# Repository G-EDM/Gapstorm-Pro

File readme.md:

</br>
</br>
</br>

```diff
 ______     _______ ______  _______
|  ____ ___ |______ |     \ |  |  |
|_____|     |______ |_____/ |  |  |
```                                                               

</br>
</br>

# G-EDM Gapstorm Pro
</br>

</br>
</br>

The files provided on this repo are fully OpenSource. Have fun. No warranties!

# (fresh update) First test for max current

I just made an initial test for max current without risking the big FET. Connected two parallel IRFP260N to the screw terminals of the board and was able to push 9.5A without breaking anything.

The big FET has a much lower RDSon resistance so there is still a chance that it may not take the full 9.5A but this looks very good so far. No warranty on that but I think the big FET will also be able to manage the full DPH8909 current.

# Warning

This repo contains the upgrade Gapstorm PCB files. I already assembled the board but did not yet had time for real tests. I made a short test shorting the wires at 2.5A and everything looked good. Feedback was very nice. Once I'm done testing, a link to PCBway will be provided and the max current rating published too. For people that have the initial Gapstorm PCB I recommend to change the Gate resistor against a 100R resistor as it is on this board. The Mosfet switching happens so rapid that very high inrush currents can occur that can damage the FET. Even with the 100R resistor the Mosfet is very very fast switching without visible slope on the ESP scope.

</br>
</br>

# About
</br>
The Gapstorm Pro is an improved version for the switching PCB used to control the discharges for EDM machines.
</br>
The PCB is not a stand alone arc generator and requires a DPM8605 or DPH8909 as external power source.
</br>
</br>

# Features
* Mosfet low side switch
* Foil pulse capacitor
* Optically isolated voltage and current feedback
* Optically isolated PWM input
</br>
</br>

# Current and Voltage ratings

* Max input voltage on the power inputs is designed to be 80V. The board has TVS and Zener protection diodes and the input should not exceed 80v. 70V is my personal sweetspot.

* In regards of max current there is still some research that needs to be done. Depending on the Gate resistor and the Foil cap there can occur very high inrush currents that can easily destroy the Mosfet. I changed the Gate resistor to a higher value to prevent this from easily happening but have not produced real max rating data as of now. The Mosfet is expenssive and I am too broke to burn through things.  I'm working on that. 
</br>
</br>

# Wiring

* The board requires a 5P JST XH wire to connect with the motionboard

* A little 12v PSU is required for the gate drive. I use a Mean Well APV-35-12 LED 12V 2.4A for that.

* DPM/DPH positive output connects to Power+ and negative to Power-. Note that those terminals are not next to eachother on this board.

* The two center terminals are the spark terminals. Spark+ connects to the work and Spark- to the electrode.

</br>
</br>

# Important Notes and Warnings

* The Mosfet requires good cooling. It can be screwed onto a heatsick or inside a metal enclosure with the PCB just sitting on top of it.
No isolation barrier between the Mosfet and the colling component is required as the SOT227 Package already provides isolation.

* The switching section is a low side switch and thereforewhile the Mosfet is active DRAIN is switched to GND
The voltage feedback is measured from Work to Electrode using a voltage divider to scale the voltage down and feed it into a sensing circuit.
The nature of this makes a measurement in the OnTime of the switching impossible since the voltage drops close to GND and the input for the sensing circuit looks like a squarewave. This allows proximity sensing but not real gap voltage sensing and then OnTime requires to be filtered out via software.

</br>
</br>

# DPM8605 or DPH8909

* One of those devices is required as source for the spark. I recommend the DPH8909 as it allows higher voltages but the DPM8605 is ok too but limited to 60V.

* Those step down converters come with different interfaces. In order to connect them to the motionboard and have the firmware communicate with them the TTL version is required. Not the RF (Radio) or RS485! Also the baudrate needs to be set at the highest available to match the baudrate used in the firmware. See the manual for the device and search for BAUD. 115200 is what it needs to be and this number is shown on the little display as 115.2 or something.

* Set the current to 1.6A or 1.8A before the first run. This is normally the current I use and safe. Voltage either 70v or if the DPM8605 is used 60v.

</br>
</br>

# G-EDM Wiki

[A little Wiki can be found here](https://gedm.org/wiki)

</br>
</br>

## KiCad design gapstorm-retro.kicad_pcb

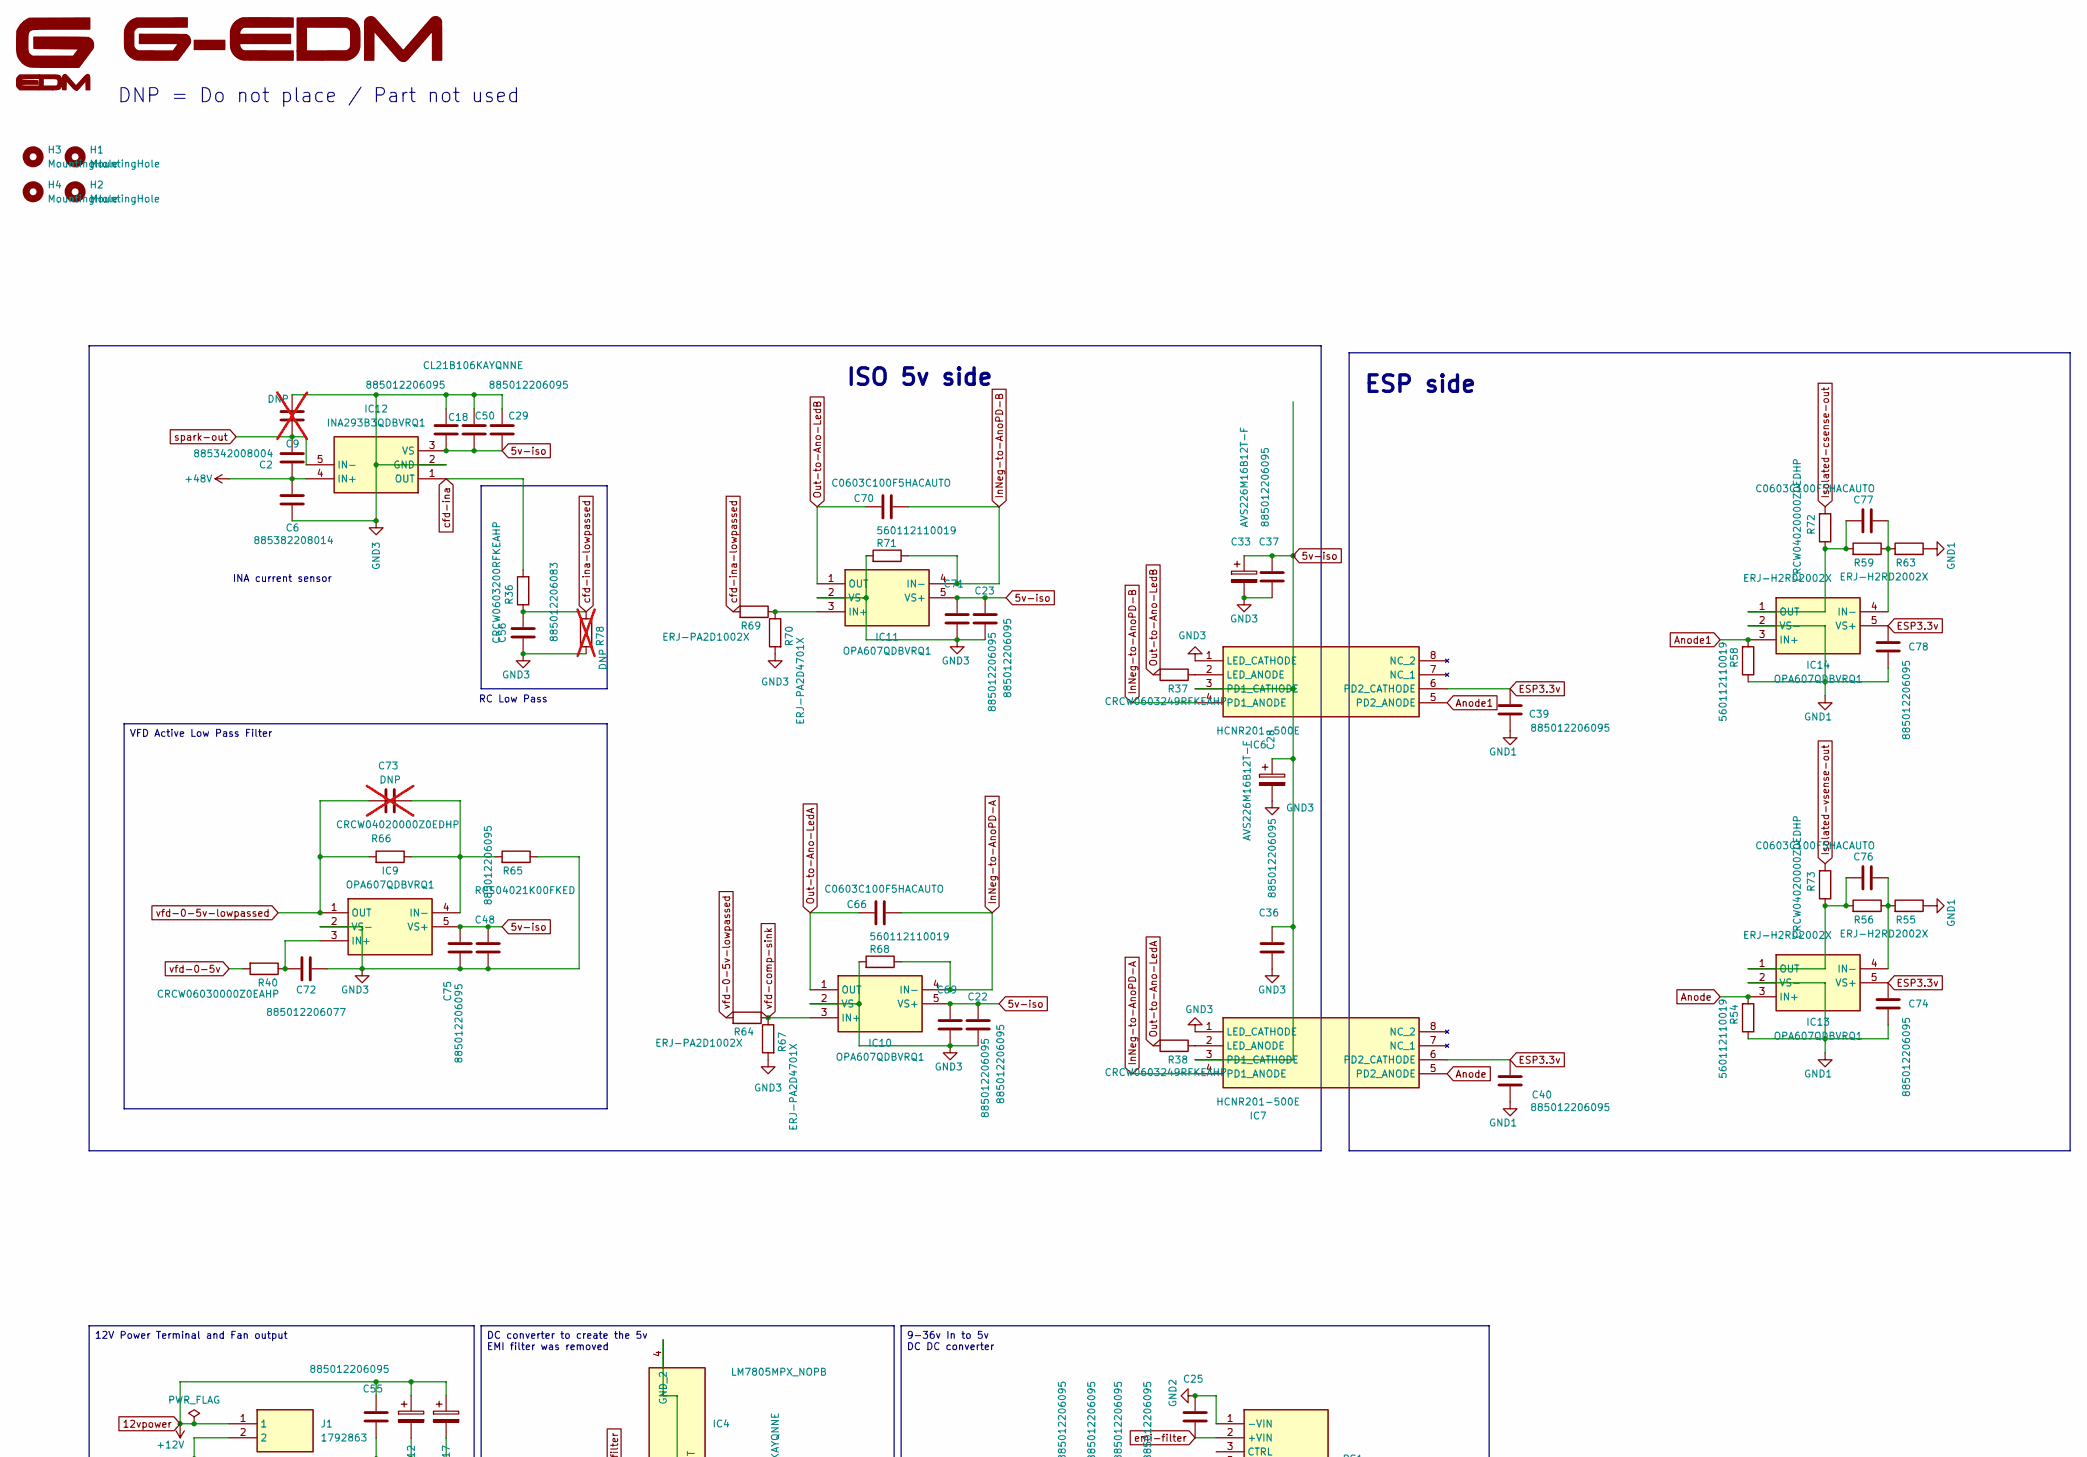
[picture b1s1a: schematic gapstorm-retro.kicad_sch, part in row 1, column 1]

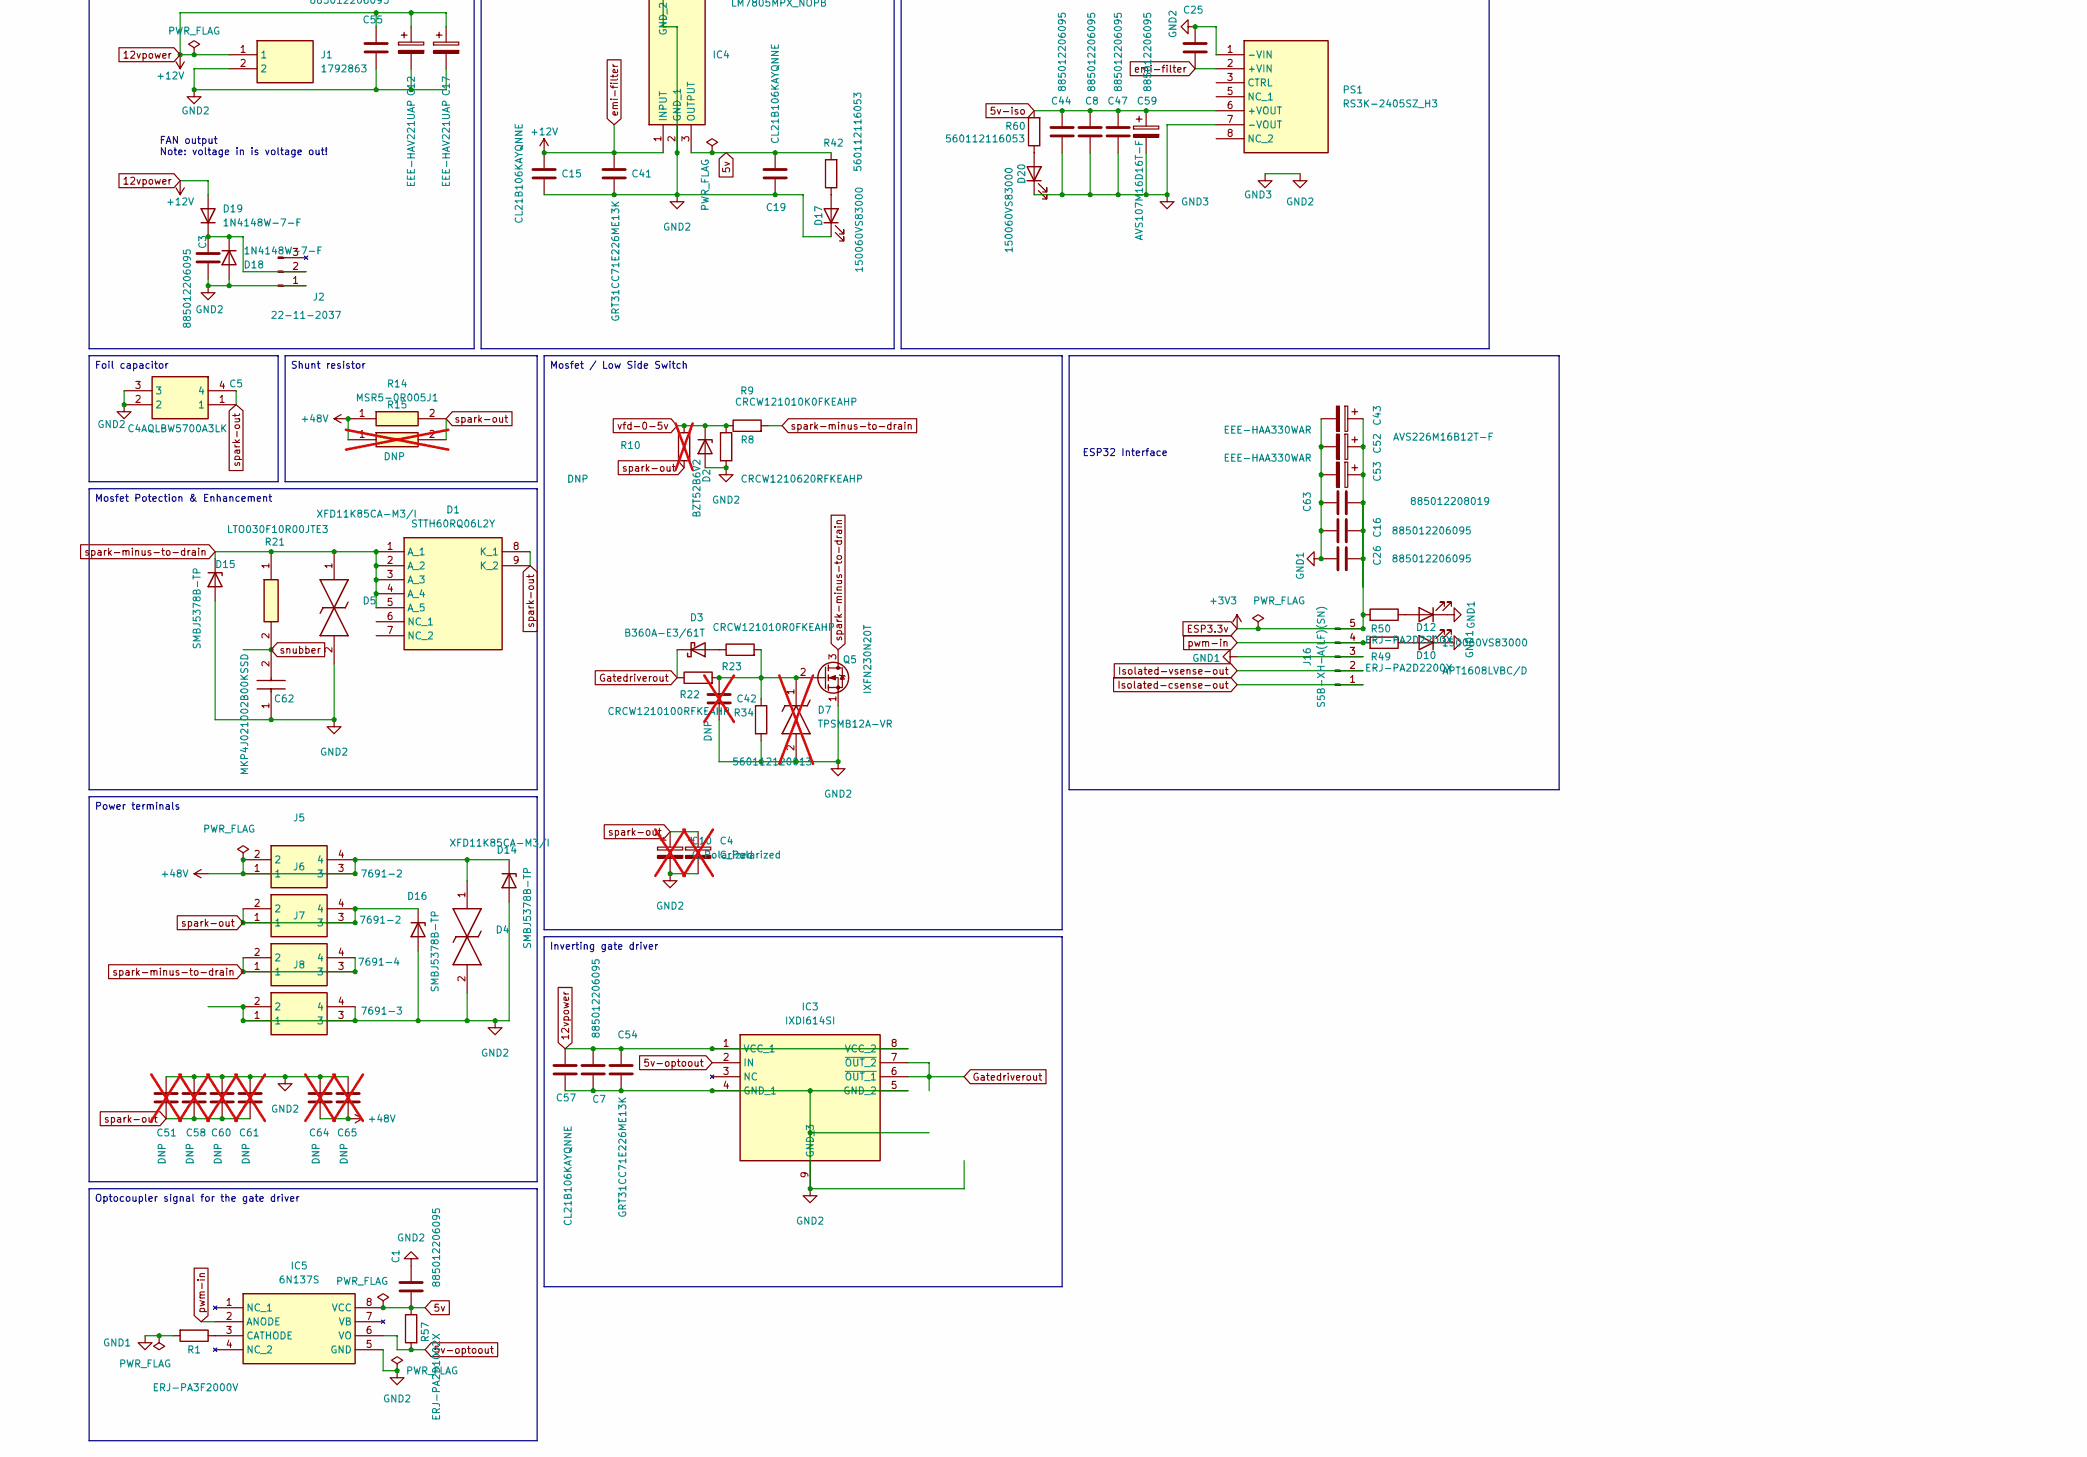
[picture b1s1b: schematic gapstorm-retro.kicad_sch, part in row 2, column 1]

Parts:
C1, C3, C7, C8, C16, C18, C22, C23, C25, C26, C29, C36, C37, C39, C40, C44, C47, C48, C55, C69, C71, C74, C75, C78: 885012206095; C_0603_1608Metric_Pad1.08x0.95mm_HandSolder
C2: 885342008004; C_1206_3216Metric_Pad1.33x1.80mm_HandSolder
C4, C10: C_Polarized; C_Radial_D12.5mm_H25.0mm_P5.00mm; not fitted
C5: C4AQLBW5700A3LK; Manufacturer_Part_Number C4AQLBW5700A3LK; Mouser Part Number 80-C4AQLBW5700A3LK
C6: 885382208014; C_1206_3216Metric_Pad1.33x1.80mm_HandSolder
C9, C42, C51, C58, C60, C61, C64, C65: DNP; C_1206_3216Metric_Pad1.33x1.80mm_HandSolder; not fitted
C12, C17: EEE-HAV221UAP; CP_Elec_8x10.5
C15, C19, C50, C57: CL21B106KAYQNNE; C_0805_2012Metric_Pad1.18x1.45mm_HandSolder
C28, C33, C43: AVS226M16B12T-F; CP_Elec_4x5.4
C41, C54: GRT31CC71E226ME13K; C_1206_3216Metric_Pad1.33x1.80mm_HandSolder
C52, C53: EEE-HAA330WAR; CP_Elec_4x5.4
C56: 885012206083; C_0603_1608Metric_Pad1.08x0.95mm_HandSolder
C59: AVS107M16D16T-F; CP_Elec_6.3x5.4
C62: MKP4J021002B00KSSD; C_Rect_L10.0mm_W4.0mm_P7.50mm_MKS4; Manufacturer_Part_Number FKP2G011001D00KI00; Mouser Part Number 505-FKP2G011001D00KI
C63: 885012208019; C_1206_3216Metric_Pad1.33x1.80mm_HandSolder
C66, C70, C76, C77: C0603C100F5HACAUTO; C_0603_1608Metric_Pad1.08x0.95mm_HandSolder
C72: 885012206077; C_0603_1608Metric_Pad1.08x0.95mm_HandSolder
C73: DNP; C_0603_1608Metric_Pad1.08x0.95mm_HandSolder; not fitted
D1: STTH60RQ06L2Y; Manufacturer_Part_Number STTH60RQ06L2Y
D2: BZT52B6V2; D_SOD-123F
D3: B360A-E3/61T; D_SMA_Handsoldering
D4, D5: XFD11K85CA-M3/I; SM8A27HE32D; Manufacturer_Part_Number PTVS1-086C-H; Mouser Part Number 652-PTVS1-086C-H
D7: TPSMB12A-VR; DIOM5436X244N; Manufacturer_Part_Number TPSMB12A-VR; Mouser Part Number 576-TPSMB12A-VR; not fitted
D10: APT1608LVBC/D; LED_0603_1608Metric_Pad1.05x0.95mm_HandSolder
D12, D17, D20: 150060VS83000; LED_0603_1608Metric_Pad1.05x0.95mm_HandSolder
D14, D15, D16: SMBJ5378B-TP; D_SMB_Handsoldering
D18, D19: 1N4148W-7-F; D_SOD-123
H1, H2, H3, H4: MountingHole; MountingHole_3.2mm_M3_Pad_Via
IC3: IXDI614SI; SOIC127P600X170-9N; Manufacturer_Part_Number IXDI614SI; Mouser Part Number 849-IXDI614SI
IC4: LM7805MPX_NOPB; SOT230P700X180-4N; Manufacturer_Part_Number LM7805MPX/NOPB; Mouser Part Number 595-LM7805MPX/NOPB
IC5: 6N137S; SOP254P1016X460-8N; Manufacturer_Part_Number 6N136S; Mouser Part Number 859-6N136S
IC6, IC7: HCNR201-500E; SOP254P1230X400-8N; Manufacturer_Part_Number HCNR201-500E; Mouser Part Number 630-HCNR201-500E
IC9, IC10, IC11, IC13, IC14: OPA607QDBVRQ1; SOT95P280X145-5N; Manufacturer_Part_Number OPA607QDBVRQ1; Mouser Part Number 595-OPA607QDBVRQ1
IC12: INA293B3QDBVRQ1; SOT95P280X145-5N; Manufacturer_Part_Number INA293B1QDBVRQ1; Mouser Part Number 595-INA293B1QDBVRQ1
J1: 1792863; Manufacturer_Part_Number 1792863; Mouser Part Number 651-1792863
J2: 22-11-2037; FanPinHeader_1x03_P2.54mm_Vertical
J5, J6: 7691-2; 8191SEMS; Manufacturer_Part_Number 8191-SEMS; Mouser Part Number 534-8191-SEMS
J7: 7691-4; 8191SEMS; Manufacturer_Part_Number 8191-SEMS; Mouser Part Number 534-8191-SEMS
J8: 7691-3; 8191SEMS; Manufacturer_Part_Number 8191-SEMS; Mouser Part Number 534-8191-SEMS
J16: S5B-XH-A(LF)(SN); JST_XH_S5B-XH-A_1x05_P2.50mm_Horizontal
PS1: RS3K-2405SZ_H3; RS3K2405SZH3; Manufacturer_Part_Number RS3K-2405SZ/H3; Mouser Part Number 919-RS3K-2405SZ/H3
Q5: IXFN230N20T; SOT-227
R1: ERJ-PA3F2000V; R_0603_1608Metric_Pad0.98x0.95mm_HandSolder
R8: CRCW1210620RFKEAHP; R_1210_3225Metric_Pad1.30x2.65mm_HandSolder
R9: CRCW121010K0FKEAHP; R_1210_3225Metric_Pad1.30x2.65mm_HandSolder
R10: DNP; R_1210_3225Metric_Pad1.30x2.65mm_HandSolder; not fitted
R14: MSR5-0R005J1; MSR50R1F1; Manufacturer_Part_Number MSR5-0R1F1
R15: DNP; MSR50R1F1; Manufacturer_Part_Number MSR5-0R1F1; not fitted
R21: LTO030F10R00JTE3; TO508P350X1040X2030-2P; Manufacturer_Part_Number LTO030F10R00JTE3; Mouser Part Number 72-LTO030F10R00JTE3
R22: CRCW1210100RFKEAHP; R_1210_3225Metric_Pad1.30x2.65mm_HandSolder
R23: CRCW121010R0FKEAHP; R_1210_3225Metric_Pad1.30x2.65mm_HandSolder
R34: 560112120013; R_0805_2012Metric_Pad1.20x1.40mm_HandSolder
R36: CRCW0603200RFKEAHP; R_0603_1608Metric_Pad0.98x0.95mm_HandSolder
R37, R38: CRCW0603249RFKEAHP; R_0603_1608Metric_Pad0.98x0.95mm_HandSolder
R40: CRCW06030000Z0EAHP; R_0603_1608Metric_Pad0.98x0.95mm_HandSolder
R42, R60: 560112116053; R_0603_1608Metric_Pad0.98x0.95mm_HandSolder
R49, R50: ERJ-PA2D2200X; R_0402_1005Metric_Pad0.72x0.64mm_HandSolder
R54, R58, R68, R71: 560112110019; R_0402_1005Metric_Pad0.72x0.64mm_HandSolder
R55, R56, R59, R63: ERJ-H2RD2002X; R_0402_1005Metric_Pad0.72x0.64mm_HandSolder
R57, R64, R69: ERJ-PA2D1002X; R_0402_1005Metric_Pad0.72x0.64mm_HandSolder
R65: RCS04021K00FKED; R_0402_1005Metric_Pad0.72x0.64mm_HandSolder
R66, R72, R73: CRCW04020000Z0EDHP; R_0402_1005Metric_Pad0.72x0.64mm_HandSolder
R67, R70: ERJ-PA2D4701X; R_0402_1005Metric_Pad0.72x0.64mm_HandSolder
R78: DNP; R_0402_1005Metric_Pad0.72x0.64mm_HandSolder; not fitted

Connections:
5v: C1.1, C19.2, IC4.3 (OUTPUT), IC5.8 (VCC), R42.2, R57.1
5v-iso: C8.2, C18.2, C22.1, C23.1, C28.1, C29.1, C33.1, C36.2, C37.2, C44.1, C47.1, C48.1, C50.1, C59.1, C69.2, C71.2, C75.1, IC6.3 (PD1_CATHODE), IC7.3 (PD1_CATHODE), IC9.5 (VS+), IC10.5 (VS+), IC11.5 (VS+), IC12.3 (VS), PS1.6 (+VOUT), R60.2
5v-optoout: IC3.2 (IN), IC5.6 (VO), R57.2
12vpower: C7.2, C12.1, C15.2, C17.1, C25.1, C41.1, C54.1, C55.1, C57.2, D19.2 (A), IC3.1 (VCC_1), IC3.8 (VCC_2), IC4.1 (INPUT), J1.1, PS1.2 (+VIN)
+48V: C2.2, C6.1, C64.1, C65.1, D4.1, D14.1 (K), IC12.4 (IN+), J5.1, J5.2, J5.3, J5.4, R14.1, R15.1
Anode: IC7.5 (PD2_ANODE), IC13.3 (IN+), R54.2
Anode1: IC6.5 (PD2_ANODE), IC14.3 (IN+), R58.2
ESP3.3v: C16.1, C26.1, C39.1, C40.1, C43.1, C52.1, C53.1, C63.2, C74.1, C78.1, IC6.6 (PD2_CATHODE), IC7.6 (PD2_CATHODE), IC13.5 (VS+), IC14.5 (VS+), J16.5, R50.2
GND1: C16.2, C26.2, C39.2, C40.2, C43.2, C52.2, C53.2, C63.1, C74.2, C78.2, D10.1 (K), D12.1 (K), IC13.2 (VS-), IC14.2 (VS-), J16.3, R1.2, R54.1, R55.1, R58.1, R63.1
GND2: C1.2, C3.1, C4.2, C5.2, C5.3, C6.2, C7.1, C8.1, C9.1, C10.2, C12.2, C15.1, C17.2, C18.1, C19.1, C22.2, C23.2, C25.2, C28.2, C29.2, C33.2, C36.1, C37.1, C41.2, C42.2, C44.2, C47.2, C48.2, C50.2, C51.2, C54.2, C55.2, C56.1, C57.1, C58.2, C59.2, C60.2, C61.2, C62.1, C64.2, C65.2, C69.1, C71.1, C72.1, C75.2, D2.2 (A), D4.2, D5.2, D7.2 (A), D14.2 (A), D15.2 (A), D16.2 (A), D17.1 (K), D18.2 (A), D20.1 (K), IC3.4 (GND_1), IC3.5 (GND_2), IC3.9 (GND_3), IC4.2 (GND_1), IC4.4 (GND_2), IC5.5 (GND), IC6.1 (LED_CATHODE), IC7.1 (LED_CATHODE), IC9.2 (VS-), IC10.2 (VS-), IC11.2 (VS-), IC12.2 (GND), J1.2, J2.1, J8.1, J8.2, J8.3, J8.4, PS1.1 (-VIN), PS1.7 (-VOUT), Q5.1 (S), Q5.4 (S), R8.2, R34.2, R65.1, R67.2, R68.2, R70.2, R71.2, R78.2
Gatedriverout: D3.1 (K), IC3.6 (~OUT_1), IC3.7 (~OUT_2), R22.1
InNeg-to-AnoPD-A: C66.2, IC7.4 (PD1_ANODE), IC10.4 (IN-), R68.1
InNeg-to-AnoPD-B: C70.2, IC6.4 (PD1_ANODE), IC11.4 (IN-), R71.1
Isolated-csense-out: J16.1, R72.2
Isolated-vsense-out: J16.2, R73.2
unnamed: D3.2 (A), R23.1
unnamed: C42.1, D7.1 (K), Q5.2 (G), R22.2, R23.2, R34.1
unnamed: D10.2 (A), R49.1
unnamed: D12.2 (A), R50.1
unnamed: D17.2 (A), R42.1
unnamed: C3.2, D18.1 (K), D19.1 (K), J2.2
unnamed: D20.2 (A), R60.1
unnamed: IC5.3 (CATHODE), R1.1
unnamed: IC6.2 (LED_ANODE), R37.1
unnamed: IC7.2 (LED_ANODE), R38.1
unnamed: C72.2, IC9.3 (IN+), R40.1
unnamed: C73.1, IC9.4 (IN-), R65.2, R66.1
unnamed: IC11.3 (IN+), R69.1, R70.1
unnamed: C76.2, IC13.4 (IN-), R55.2, R56.1
unnamed: C76.1, IC13.1 (OUT), R56.2, R73.1
unnamed: C77.2, IC14.4 (IN-), R59.1, R63.2
unnamed: C77.1, IC14.1 (OUT), R59.2, R72.1
Out-to-Ano-LedA: C66.1, IC10.1 (OUT), R38.2
Out-to-Ano-LedB: C70.1, IC11.1 (OUT), R37.2
cfd-ina: IC12.1 (OUT), R36.2
cfd-ina-lowpassed: C56.2, R36.1, R69.2, R78.1
pwm-in: IC5.2 (ANODE), J16.4, R49.2
snubber: C62.2, R21.2
spark-minus-to-drain: D1.1 (A_1), D1.2 (A_2), D1.3 (A_3), D1.4 (A_4), D1.5 (A_5), D5.1, D15.1 (K), J7.1, J7.2, J7.3, J7.4, Q5.3 (D), R9.2, R21.1
spark-out: C2.1, C4.1, C5.1, C5.4, C9.2, C10.1, C51.1, C58.1, C60.1, C61.1, D1.8 (K_1), D1.9 (K_2), D16.1 (K), IC12.5 (IN-), J6.1, J6.2, J6.3, J6.4, R10.2, R14.2, R15.2
vfd-0-5v: D2.1 (K), R8.1, R9.1, R10.1, R40.2
vfd-0-5v-lowpassed: C73.2, IC9.1 (OUT), R64.2, R66.2
vfd-comp-sink: IC10.3 (IN+), R64.1, R67.1

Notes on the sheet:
FAN output Note: voltage in is voltage out!
DNP = Do not place / Part not used
RC Low Pass
ESP32 Interface
INA current sensor
ESP side
ISO 5v side
VFD Active Low Pass Filter
Shunt resistor
Power terminals
Inverting gate driver
12V Power Terminal and Fan output
Foil capacitor
Optocoupler signal for the gate driver
Mosfet / Low Side Switch
Mosfet Potection & Enhancement
9-36v In to 5v DC DC converter
DC converter to create the 5v EMI filter was removed

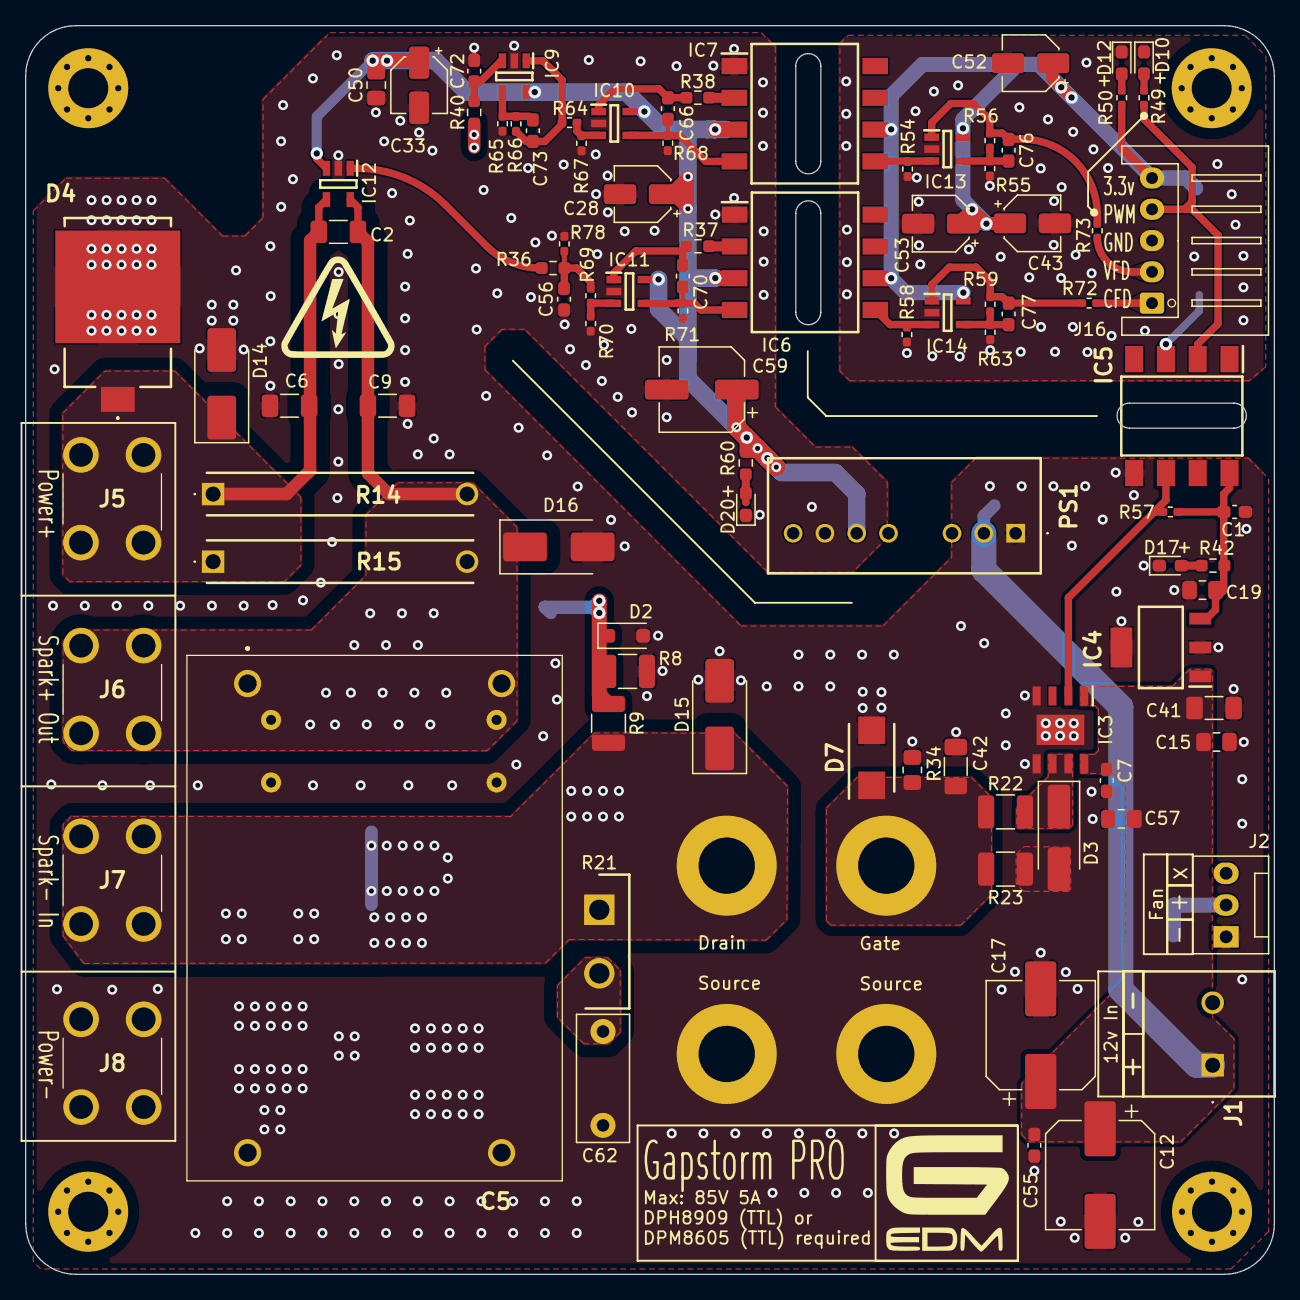
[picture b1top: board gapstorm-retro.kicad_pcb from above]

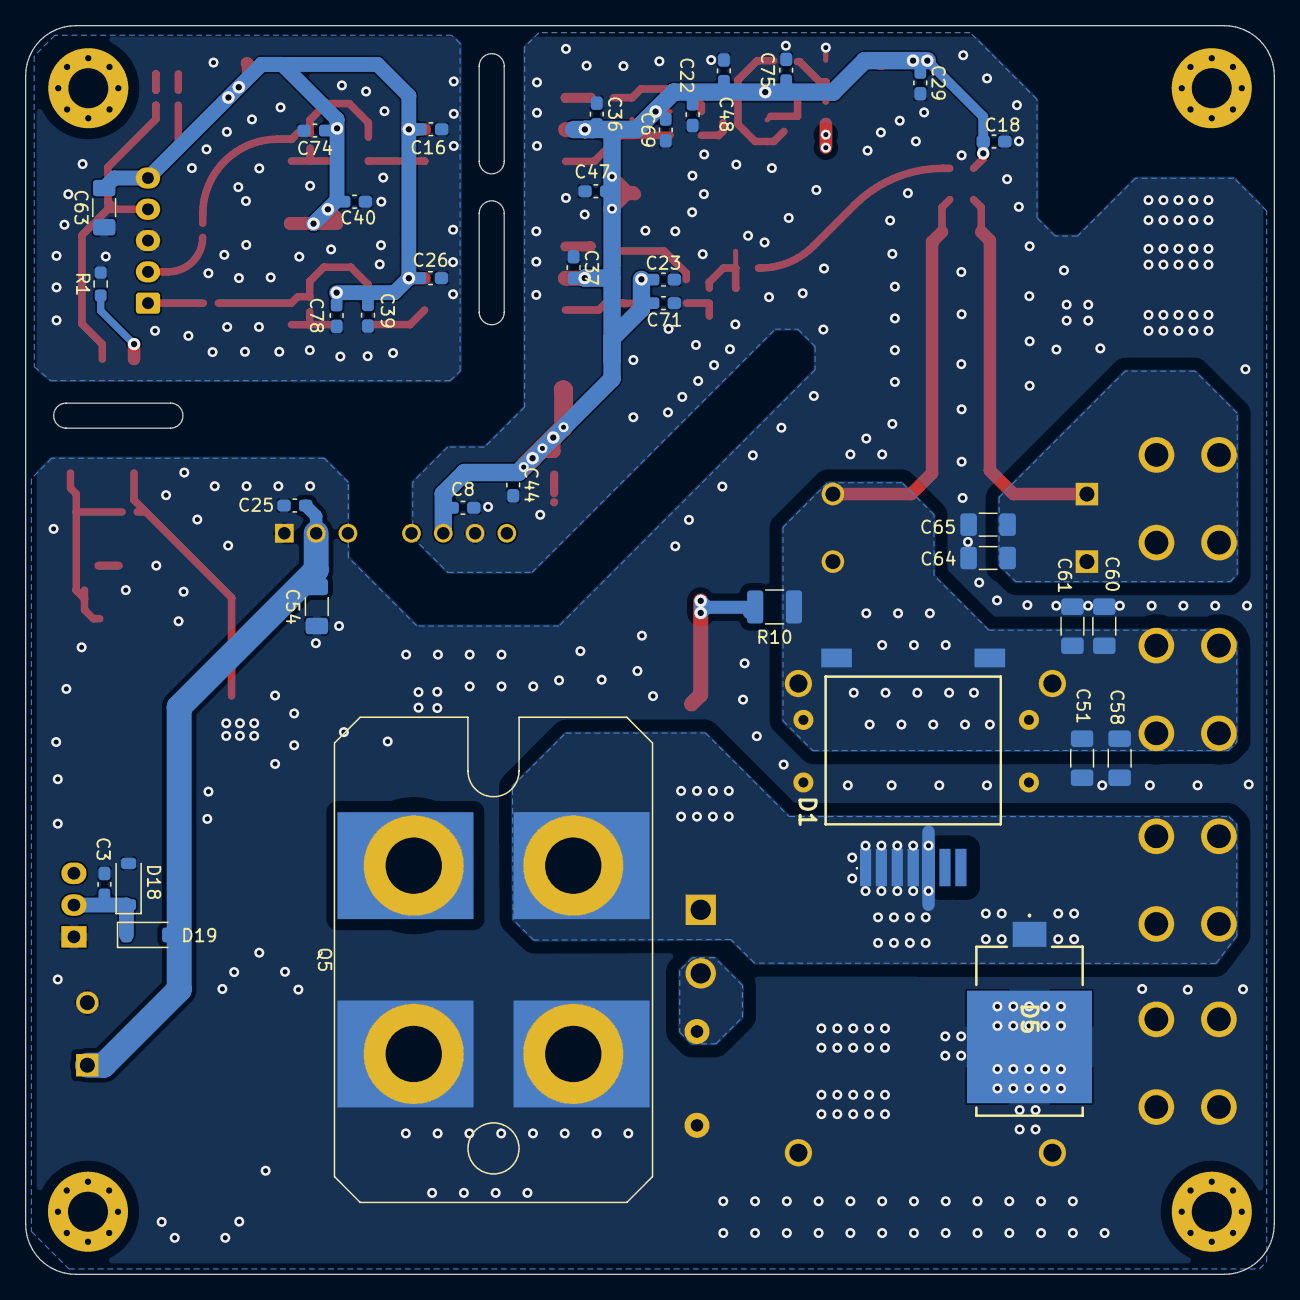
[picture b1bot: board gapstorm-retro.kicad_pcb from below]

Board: 4 copper layers, 99.8 x 99.8 mm, 135 parts (36 on the bottom side), 43 nets.

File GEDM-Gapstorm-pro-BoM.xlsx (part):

|  |  | G-EDM Pulseboard Gapstorm Pro
Item # | *Designator | *Qty | Manufacturer | *Mfg Part # | Description / Value | *Package/Footprint | Type | Comments
1 | C1, C3, C7, C8, C16, C18, C22, C23, C26, C36, C37, C39, C40, C47, C48, C55, C69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 | 24 | Würth Elektronik | 885012206095 | Multilayer Ceramic Capacitors MLCC - SMD/SMT WCAP-CSGP 0.1uF 0603 10% 50V MLCC | C_0603_1608Metric_Pad1.08x0.95mm_HandSolder | SMD
2 | C2 | 1 | Würth Elektronik | 885342008004 | Multilayer Ceramic Capacitors MLCC - SMD/SMT WCAP-CSMH 630V 100pF 1206 5% | C_1206_3216Metric_Pad1.33x1.80mm_HandSolder | SMD
3 | C4, C10 | 0 |  |  | Do not place / Part not used | C_Radial_D12.5mm_H25.0mm_P5.00mm | THT | Do not place / Part not used
4 | C5 | 1 | KEMET | C4AQLBW5700A3LK | Film Capacitors 500V 70 uF 105C 10% 4 Pin LS=37.5 mm AEC-Q200 | C4AQLBW5700A3LK | THT
5 | C6 | 1 | Würth Elektronik | 885382208014 | Multilayer Ceramic Capacitors MLCC - SMD/SMT WCAP-CSST 1206 680pF 10% 2000VDC | C_1206_3216Metric_Pad1.33x1.80mm_HandSolder | SMD
6 | C9, C42, C51, C58, C60, C61, C64, C65 | 0 |  |  | Do not place / Part not used | C_1206_3216Metric_Pad1.33x1.80mm_HandSolder | SMD | Do not place / Part not used
7 | C12, C17 | 2 | Panasonic Industry | EEE-HAV221UAP | Aluminium Electrolytic Capacitors - SMD 220UF 35V HA SMD | CP_Elec_8x10.5 | SMD
8 | C15, C19, C50, C57 | 4 | Samsung Electro-Mechanics | CL21B106KAYQNNE | Multilayer Ceramic Capacitors MLCC - SMD/SMT 10uF 25V X7R 10% 080 0805 | C_0805_2012Metric_Pad1.18x1.45mm_HandSolder | SMD
9 | C28, C33, C43 | 3 | Knowles / Illinois Capacitor | AVS226M16B12T-F | Aluminium Electrolytic Capacitors - SMD 16V 22uF AEC-Q200 | CP_Elec_4x5.4 | SMD
10 | C41, C54 | 2 | Murata Electronics | GRT31CC71E226ME13K | Multilayer Ceramic Capacitors MLCC - SMD/SMT 1206 22uF 25VDC 20% X7S AEC-Q200 | C_1206_3216Metric_Pad1.33x1.80mm_HandSolder | SMD
11 | C52, C53 | 2 | Panasonic Industry | EEE-HAA330WAR | Aluminium Electrolytic Capacitors - SMD 33UF 10V HA SMD | CP_Elec_4x5.4 | SMD
12 | C56 | 1 | Würth Elektronik | 885012206083 | Multilayer Ceramic Capacitors MLCC - SMD/SMT WCAP-CSGP 1000pF 0603 10% 50V MLCC | C_0603_1608Metric_Pad1.08x0.95mm_HandSolder | SMD
13 | C59 | 1 | Knowles / Illinois Capacitor | AVS107M16D16T-F | Aluminium Electrolytic Capacitors - SMD 16V 100uF AEC-Q200 | CP_Elec_6.3x5.4 | SMD
14 | C62 | 1 | WIMA | MKP4J021002B00KSSD | Film Capacitors 630V .01uF 10% | C_Rect_L10.0mm_W4.0mm_P7.50mm_MKS4 | THT
15 | C63 | 1 | Würth Elektronik | 885012208019 | Multilayer Ceramic Capacitors MLCC - SMD/SMT WCAP-CSGP 22uF 1206 10% 10V MLCC | C_1206_3216Metric_Pad1.33x1.80mm_HandSolder | SMD
16 | C66, C70, C76, C77 | 4 | KEMET | C0603C100F5HACAUTO | Multilayer Ceramic Capacitors MLCC - SMD/SMT 50V 10pF 0603 X8R 1% AEC-Q200 | C_0603_1608Metric_Pad1.08x0.95mm_HandSolder | SMD
17 | C72 | 1 | Würth Elektronik | 885012206077 | Multilayer Ceramic Capacitors MLCC - SMD/SMT WCAP-CSGP 100pF 0603 10% 50V MLCC | C_0603_1608Metric_Pad1.08x0.95mm_HandSolder | SMD
18 | C73 | 0 |  |  | Do not place / Part not used | C_0603_1608Metric_Pad1.08x0.95mm_HandSolder | SMD | Do not place / Part not used
19 | D1 | 1 | STMicroelectronics | STTH60RQ06L2Y | Rectifiers Automotive 600 V, 60 A ultrafast high voltage rectifier | STTH60RQ06L2Y | SMD
20 | D2 | 0 |  |  | Do not place / Part not used | D_SOD-123F | SMD | Do not place / Part not used
21 | D3 | 1 | Vishay Semiconductors | B360A-E3/61T | Schottky Diodes & Rectifiers 60 Volt 3.0 Amp 50 Amp IFSM | D_SMA_Handsoldering | SMD
22 | D4, D5 | 2 | Vishay Semiconductors | XFD11K85CA-M3/I | ESD Protection Diodes / TVS Diodes 11KW, 85V 5%, SMD FlatClamping TVS | SM8A27HE32D | SMD
23 | D7 | 0 |  |  | Do not place / Part not used | DIOM5436X244N | SMD | Do not place / Part not used
24 | D10 | 1 | Kingbright | APT1608LVBC/D | Single Colour LEDs 1.6X0.8MM LOW CRNT | LED_0603_1608Metric_Pad1.05x0.95mm_HandSolder | SMD
25 | D12, D17, D20 | 3 | Würth Elektronik | 150060VS83000 | Single Colour LEDs WL-SMCW SMT 0603 Dome Bright Green Typ 300mcd 2V | LED_0603_1608Metric_Pad1.05x0.95mm_HandSolder | SMD
26 | D14, D15, D16 | 3 | Micro Commercial Components (MCC) | SMBJ5378B-TP | Zener Diodes 5W ZENERS SMB 100V | D_SMB_Handsoldering | SMD
27 | D18, D19 | 2 | Diodes Incorporated | 1N4148W-7-F | Small Signal Switching Diodes SURFACE MOUNT FAST SWITCHING DIODE 2A | D_SOD-123 | SMD
28 | IC3 | 1 | IXYS Integrated Circuits | IXDI614SI | Gate Drivers 14-Ampere Low-Side Ultrafast MOSFET Inverting | SOIC127P600X170-9N | SMD
29 | IC4 | 1 | Texas Instruments | LM7805MPX_NOPB | Linear Voltage Regulators 1.5-A 30-V linear vo ltage regulator 4- A 595-LM7805M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 | SOT230P700X180-4N | SMD
30 | IC5 | 1 | LITEON | 6N137S | High Speed Optocouplers High Speed 10MBd LogicGate Output | SOP254P1016X460-8N | SMD
31 | IC6, IC7 | 2 | Broadcom / Avago | HCNR201-500E | High Linearity Optocouplers 1 Ch 60mW 25mA | SOP254P1230X400-8N | SMD
32 | IC9, IC10, IC11, IC13, IC14 | 5 | Texas Instruments | OPA607QDBVRQ1 | High Speed Operational Amplifiers Automotive 50-MHz lo w-power gain of 6 | SOT95P280X145-5N | SMD
33 | IC12 | 1 | Texas Instruments | INA293B3QDBVRQ1 | Current Sense Amplifiers AEC-Q100 -4-V to 11 0-V 1.3-MHz ultra-fast | SOT95P280X145-5N | SMD
34 | J1 | 1 | Phoenix Contact | 1792863 | Fixed Terminal Blocks PTS 1,5/ 2-5,0-H | 1792863 | THT
35 | J2 | 1 | Molex | 22-11-2037 | Headers & Wire Housings KK 100 Hdr FrLk Vert 3CKT - 2P Voided | FanPinHeader_1x03_P2.54mm_Vertical | THT
36 | J5, J6 | 2 | Keystone Electronics | 7691-2 | Terminals SCREW TERMINAL RED | 8191SEMS | THT
37 | J7 | 1 | Keystone Electronics | 7691-4 | Terminals SCREW TERMINAL WHITE | 8191SEMS | THT
38 | J8 | 1 | Keystone Electronics | 7691-3 | Terminals SCREW TERMINAL BLACK | 8191SEMS | THT
39 | J16 | 1 | JST Commercial | S5B-XH-A(LF)(SN) | Headers & Wire Housings XH HEADER (SIDE) | JST_XH_S5B-XH-A_1x05_P2.50mm_Horizontal | THT
40 | PS1 | 1 | RECOM Power | RS3K-2405SZ/H3 | DC/DC Converters - Through Hole 3W 9-36Vin 5Vout 600mA | RS3K-2405SZ_H3 | THT
41 | Q5 | 1 | IXYS | IXFN230N20T | MOSFET Modules 230A 200V | SOT-227 | Screw mount
42 | R1 | 1 | Panasonic Industry | ERJ-PA3F2000V | Thick Film Resistors - SMD 0603 200ohm 1% Anti-Surge AEC-Q200 | R_0603_1608Metric_Pad0.98x0.95mm_HandSolder | SMD
43 | R8 | 1 | Vishay | CRCW1210620RFKEAHP | Thick Film Resistors - SMD 2.5W 620ohms 1% High Power AEC-Q200 | R_1210_3225Metric_Pad1.30x2.65mm_HandSolder | SMD
44 | R9 | 1 | Vishay | CRCW121010K0FKEAHP | Thick Film Resistors - SMD 2.5W 10Kohms 1% High Power AEC-Q200 | R_1210_3225Metric_Pad1.30x2.65mm_HandSolder | SMD
45 | R10 | 0 |  |  | Do not place / Part not used | R_1210_3225Metric_Pad1.30x2.65mm_HandSolder | SMD | Do not place / Part not used
46 | R14 | 1 | Bourns | MSR5-0R005J1 | Current Sense Resistors - Through Hole MSR-5 0.005 OHM 5% FLAT | MSR50R1F1 | THT
47 | R15 | 0 |  |  | Do not place / Part not used | MSR50R1F1 | THT | Do not place / Part not used
48 | R21 | 1 | Vishay / Sfernice | LTO030F10R00JTE3 | Thick Film Resistors - Through Hole 10ohms 5% | TO508P350X1040X2030-2P | THT
49 | R22 | 1 | Vishay | CRCW1210100RFKEAHP | Thick Film Resistors - SMD 2.5W 100ohms 1% High Power AEC-Q200 | R_1210_3225Metric_Pad1.30x2.65mm_HandSolder | SMD
50 | R23 | 1 | Vishay | CRCW121010R0FKEAHP | Thick Film Resistors - SMD 2.5W 10ohms 1% High Power AEC-Q200 | R_1210_3225Metric_Pad1.30x2.65mm_HandSolder | SMD
51 | R34 | 1 | Würth Elektronik | 560112120013 | Thick Film Resistors - SMD WRIS-RSKS 100 kOhms 1 % 0.25 W 0805 AEC-Q200 | R_0805_2012Metric_Pad1.20x1.40mm_HandSolder | SMD
52 | R36 | 1 | Vishay | CRCW0603200RFKEAHP | Thick Film Resistors - SMD 0.75W 200ohm 1% High Power AEC-Q200 | R_0603_1608Metric_Pad0.98x0.95mm_HandSolder | SMD
53 | R37, R38 | 2 | Vishay | CRCW0603249RFKEAHP | Thick Film Resistors - SMD 0.75W 249 Ohms 1% High Power AEC-Q200 | R_0603_1608Metric_Pad0.98x0.95mm_HandSolder | SMD
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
